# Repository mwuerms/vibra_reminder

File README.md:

# vibra_reminder
a vibra alarm, worn at your ankle. It reminds you every ca. XY min (ex. 30 min) to be mindful, to do a reality check, ... (or perform what ever task you want to be reminded of)

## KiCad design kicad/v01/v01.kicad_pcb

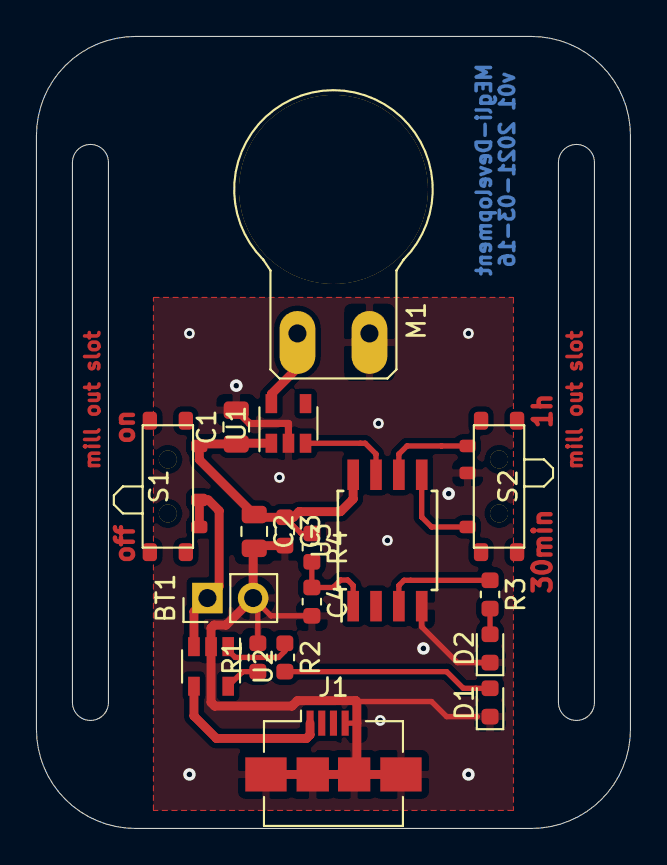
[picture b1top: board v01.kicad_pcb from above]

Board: 2 copper layers, 33.0 x 44.0 mm, 18 parts (0 on the bottom side), 14 nets.

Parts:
BT1: Battery_Cell; PinHeader_1x02_P2.54mm_Vertical
C1, C2: 10uF; C_0805_2012Metric
C3, C4: 100nF; C_0603_1608Metric
D1, D2: LED; LED_0603_1608Metric
J1: USB_B_Micro; USB_Micro-B_Amphenol_10104110_Horizontal
M1: Vibramotor
R1, R4: 10k; R_0603_1608Metric
R2: R; R_0603_1608Metric
R3: 1k; R_0603_1608Metric
S1, S2: PCM12SMTR
U1: MCP1802T-xxIOT; SOT-23-5
U2: MCP73831T-2xxIOT; SOT-23-5
U3: ATtiny85-20SU; SOIJ-8_5.3x5.3mm_P1.27mm

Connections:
+BATT: BT1.1, S1.2, S1.3, U2.3
GND: BT1.2, C1.2, C2.2, C3.2, C4.2, D1.1, D2.1, J1.4, J1.5, J1.6, M1.2, R1.2, S2.2, U1.2, U2.2, U3.4
unnamed: C1.1, C2.1, C3.1, R4.1, S1.1, U1.1, U3.8
unnamed: C4.1, R4.2, U3.1
unnamed: D1.2, R2.2
unnamed: D2.2, R3.2
unnamed: M1.1, U1.5
unnamed: R1.1, U2.5
unnamed: R2.1, U2.1
unnamed: R3.1, U3.3
unnamed: S2.1, U3.5
unnamed: S2.3, U3.6
unnamed: U1.3, U3.7
VBUS: J1.1, U2.4

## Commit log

2021-03-02 v01: schematics basically done
2021-03-03 installed and setup avr-gcc toolchain for windows
2021-03-06 some layout
2021-03-06 started attiny85 avr-gcc code project by copying from other project
2021-03-08 v01: added some footprints and did some placing
2021-03-15 v01: 100% routed, ready for pcb production
    ordered from jlcpcb
2021-03-17 1st testing software
2021-03-19 create case vc01
2021-04-26 changed case, also vibra every 45 min
